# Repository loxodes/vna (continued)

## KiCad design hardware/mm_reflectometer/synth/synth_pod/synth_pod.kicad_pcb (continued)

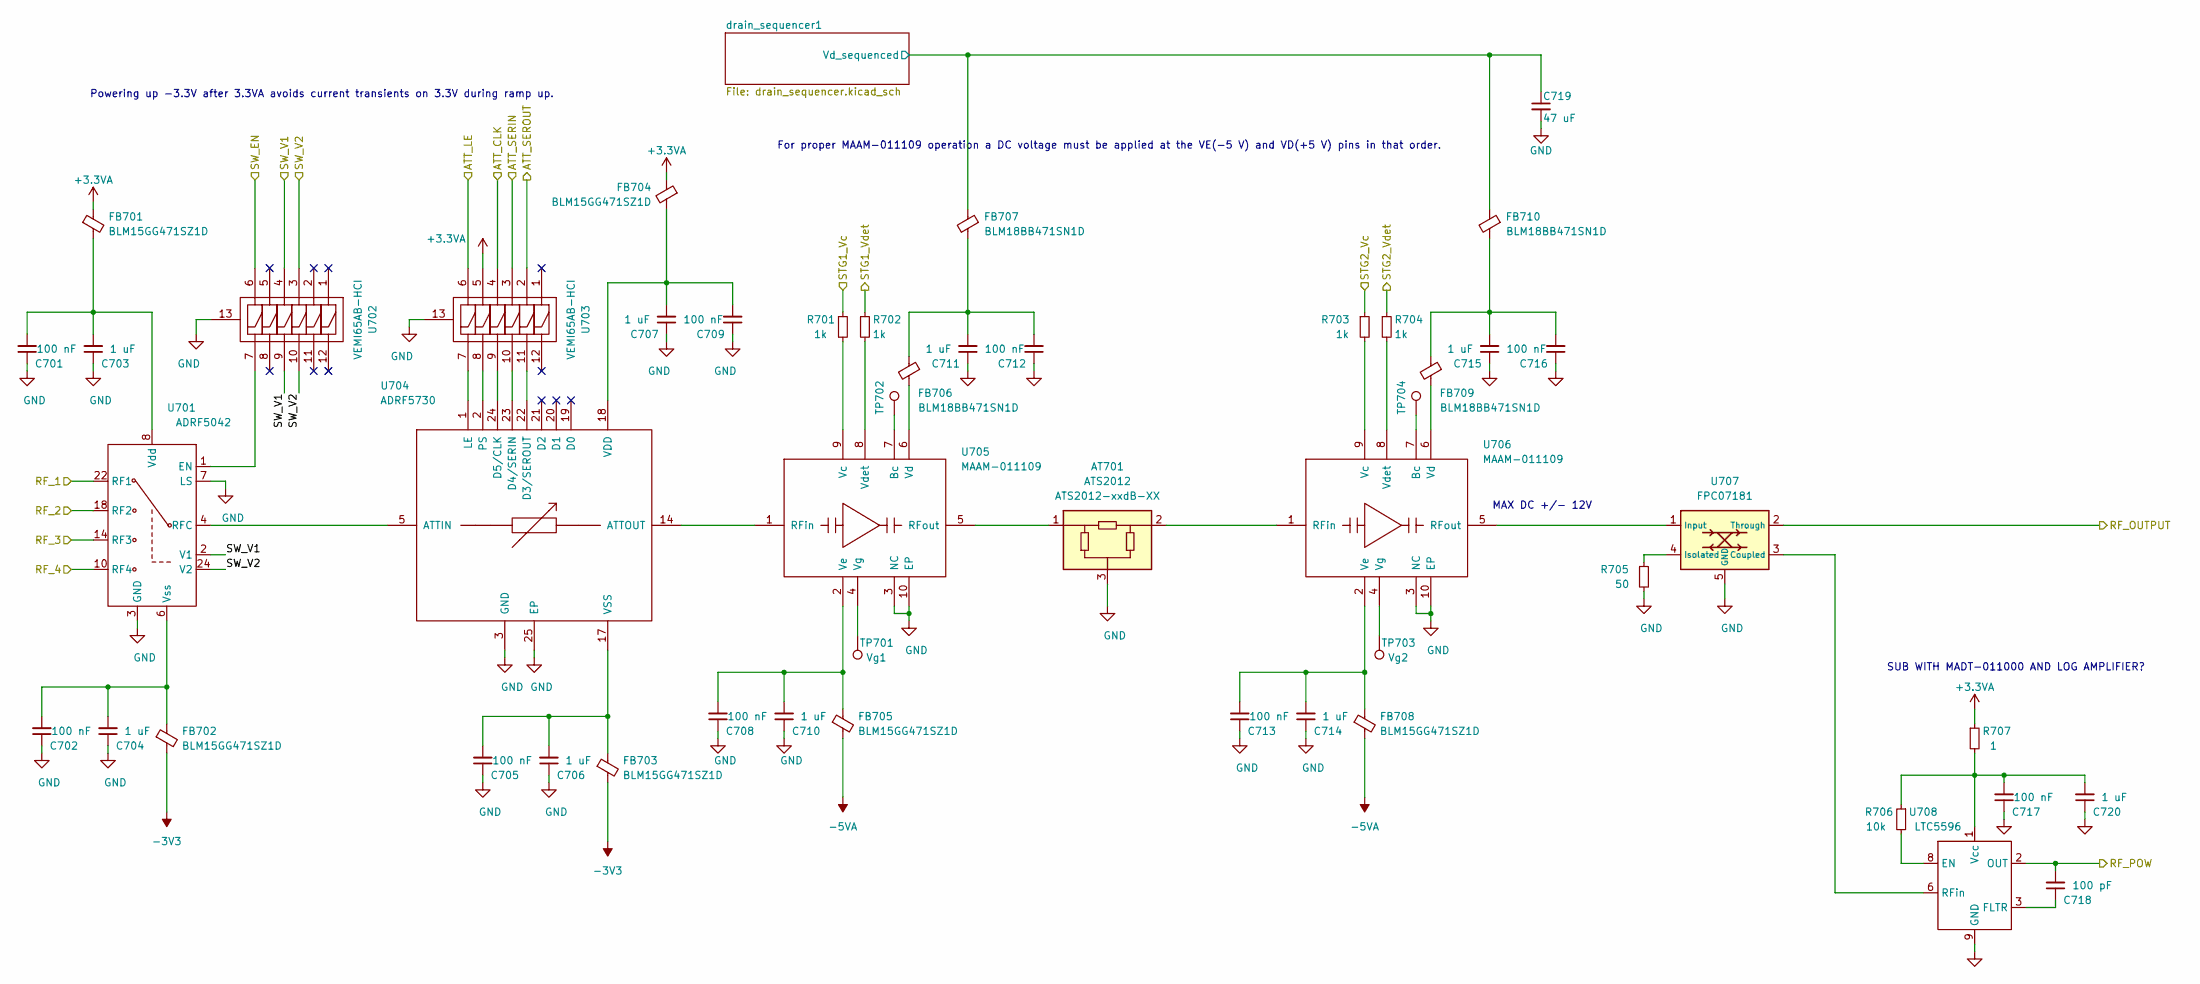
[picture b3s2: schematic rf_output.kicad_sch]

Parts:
AT701: ATS2012; mpn ATS2012-xxdB-XX
C701, C702, C705, C708, C709, C712, C713, C716, C717: 100 nF; C_0402_1005Metric
C703, C704, C706, C707, C710, C711, C714, C715, C720: 1 uF; C_0402_1005Metric
C718: 100 pF; C_0402_1005Metric
C719: 47 uF; CP_EIA-3528-15_AVX-H
FB701, FB702, FB703, FB704, FB705, FB708: BLM15GG471SZ1D; L_0402_1005Metric
FB706, FB707, FB709, FB710: BLM18BB471SN1D; L_0603_1608Metric
R701, R702, R703, R704: 1k; R_0402_1005Metric
R705: 50; R_0402_1005Metric
R706: 10k; R_0402_1005Metric
R707: 1; R_0402_1005Metric
TP701: Vg1; TestPoint_Pad_D1.5mm
TP702: Bc1; TestPoint_Pad_D1.5mm
TP703: Vg2; TestPoint_Pad_D1.5mm
TP704: Bc2; TestPoint_Pad_D1.5mm
U701: ADRF5042; LGA-24-1EP_3x3mm_P0.4mm_EP1.5x1.5mm_ADI_CC_24_12; mpn ADRF5042BCCZN; digikey# 505-ADRF5042BCCZN-ND
U702, U703: VEMI65AB-HCI; LLP2513-13L
U704: ADRF5730; LGA-24_EP_4x4_Pitch0.5mm; mpn ADRF5730BCCZN; digikey# ADRF5730BCCZN-ND
U705, U706: MAAM-011109; MACOM_LGA9; mpn MAAM-011109-TR1000; digikey# 1465-1284-1-ND
U707: FPC07181; mpn FPC07181; digikey# 1761-1032-ND
U708: LTC5596; DFN-8-1EP_2x2mm_P0.5mm_EP0.25x1.6mm

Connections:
+3.3VA: FB701.1, FB704.1, R707.1, U703.5; also elsewhere on the board
-3V3: FB702.2, FB703.2; also elsewhere on the board
-5VA: FB705.2, FB708.2; also elsewhere on the board
/ATT_CLK: U703.4; also elsewhere on the board
/ATT_LE: U703.6; also elsewhere on the board
/ATT_SERIN: U703.3; also elsewhere on the board
/ATT_SEROUT: U703.2; also elsewhere on the board
/OUT_SW_EN: U702.6; also elsewhere on the board
/OUT_SW_V1: U701.2 (V1), U702.4, U702.9; also elsewhere on the board
/OUT_SW_V2: U701.24 (V2), U702.3, U702.10; also elsewhere on the board
/RF_POW: C718.2, U708.2 (OUT); also elsewhere on the board
/STG1_Vc: R701.1; also elsewhere on the board
/STG1_Vdet: R702.1; also elsewhere on the board
/STG2_Vc: R703.1; also elsewhere on the board
/STG2_Vdet: R704.1; also elsewhere on the board
/bypass/BYPASS_OUT: U701.22 (RF1); also elsewhere on the board
/fundamental_a/FUND_A_OUT: U701.18 (RF2); also elsewhere on the board
/fundamental_b/FUND_B_OUT: U701.14 (RF3); also elsewhere on the board
/highband/HIGHBAND_OUT: U701.10 (RF4); also elsewhere on the board
/panel/RF_OUTPUT: U707.2 (Through); also elsewhere on the board
/rf_output/drain_sequencer1/Vd_sequenced: C719.1, FB707.1, FB710.1; also elsewhere on the board
GND: AT701.3, C701.1, C702.1, C703.1, C704.1, C705.1, C706.1, C707.1, C708.1, C709.1, C710.1, C711.1, C712.1, C713.1, C714.1, C715.1, C716.1, C717.1, C719.2, C720.1, R705.2, U701.3 (GND), U701.5 (GND), U701.7 (LS), U701.9 (GND), U701.11 (GND), U701.12 (GND), U701.13 (GND), U701.15 (GND), U701.16 (GND), U701.17 (GND), U701.19 (GND), U701.20 (GND), U701.21 (GND), U701.23 (GND), U701.25 (GND), U702.13, U703.13, U704.3 (GND), U704.4 (GND), U704.6 (GND), U704.7 (GND), U704.8 (GND), U704.9 (GND), U704.10 (GND), U704.11 (GND), U704.12 (GND), U704.13 (GND), U704.15 (GND), U704.16 (GND), U704.25 (EP), U705.3 (NC), U705.10 (EP), U706.3 (NC), U706.10 (EP), U707.5 (GND), U708.4 (GND), U708.5 (GND), U708.7 (GND), U708.9 (GND); also elsewhere on the board
unnamed: AT701.1, U705.5 (RFout)
unnamed: AT701.2, U706.1 (RFin)
unnamed: C701.2, C703.2, FB701.2, U701.8 (Vdd)
unnamed: C702.2, C704.2, FB702.1, U701.6 (Vss)
unnamed: C705.2, C706.2, FB703.1, U704.17 (VSS)
unnamed: C707.2, C709.2, FB704.2, U704.18 (VDD)
unnamed: C708.2, C710.2, FB705.1, U705.2 (Ve)
unnamed: C711.2, C712.2, FB706.1, FB707.2
unnamed: C713.2, C714.2, FB708.1, U706.2 (Ve)
unnamed: C715.2, C716.2, FB709.1, FB710.2
unnamed: C717.2, C720.2, R706.1, R707.2, U708.1 (Vcc)
unnamed: C718.1, U708.3 (FLTR)
unnamed: FB706.2, U705.6 (Vd)
unnamed: FB709.2, U706.6 (Vd)
unnamed: R701.2, U705.9 (Vc)
unnamed: R702.2, U705.8 (Vdet)
unnamed: R703.2, U706.9 (Vc)
unnamed: R704.2, U706.8 (Vdet)
unnamed: R705.1, U707.4 (Isolated)
unnamed: R706.2, U708.8 (EN)
unnamed: TP701.1, U705.4 (Vg)
unnamed: TP702.1, U705.7 (Bc)
unnamed: TP703.1, U706.4 (Vg)
unnamed: TP704.1, U706.7 (Bc)
unnamed: U701.1 (EN), U702.7
unnamed: U701.4 (RFC), U704.5 (ATTIN)
unnamed: U703.7, U704.1 (LE)
unnamed: U703.8, U704.2 (PS)
unnamed: U703.9, U704.24 (D5/CLK)
unnamed: U703.10, U704.23 (D4/SERIN)
unnamed: U703.11, U704.22 (D3/SEROUT)
unnamed: U704.14 (ATTOUT), U705.1 (RFin)
unnamed: U706.5 (RFout), U707.1 (Input)
unnamed: U707.3 (Coupled), U708.6 (RFin)

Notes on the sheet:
Powering up -3.3V after 3.3VA avoids current transients on 3.3V during ramp up.
MAX DC +/- 12V
For proper MAAM-011109 operation a DC voltage must be applied at the VE(-5 V) and VD(+5 V) pins in that order.
SUB WITH MADT-011000 AND LOG AMPLIFIER?

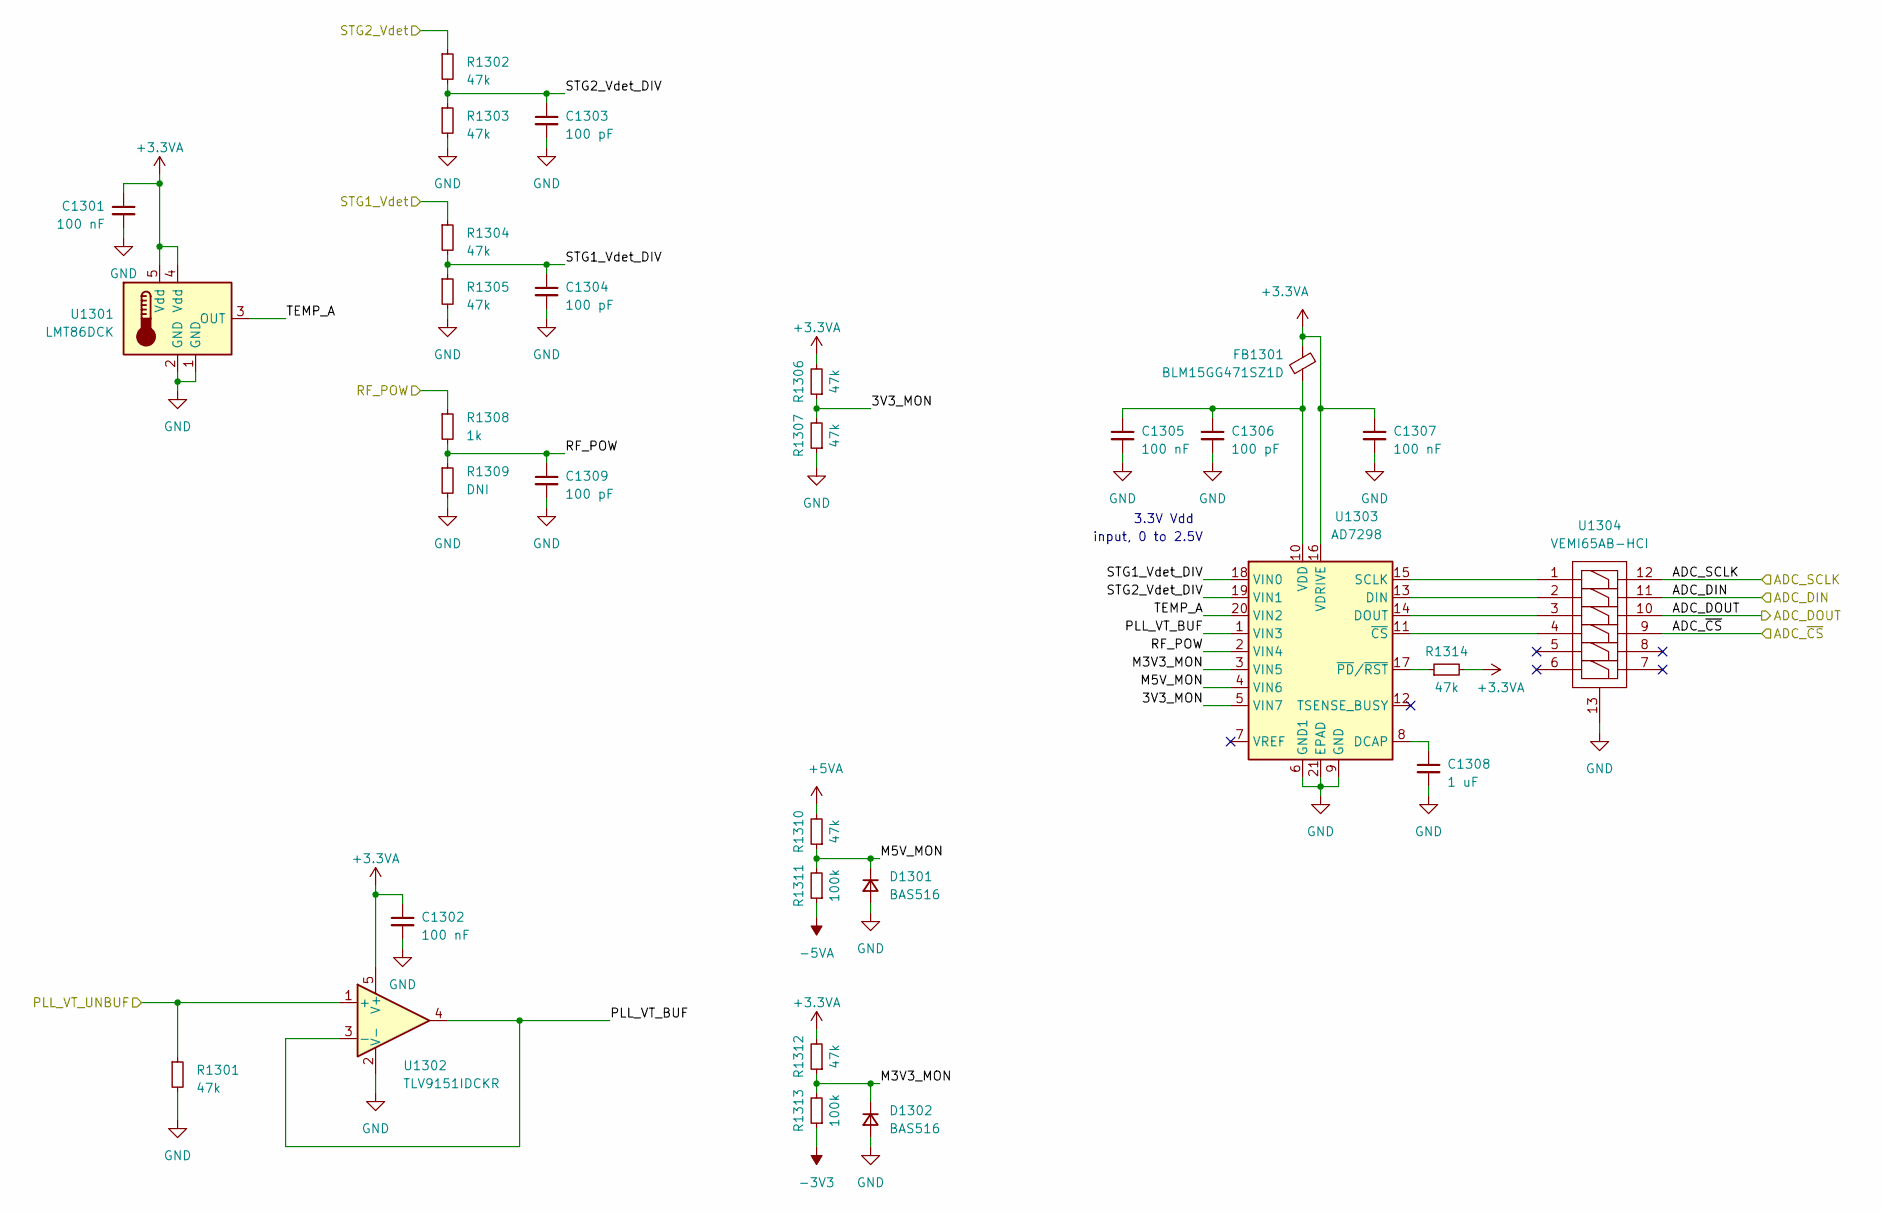
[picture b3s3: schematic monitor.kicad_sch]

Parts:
C1301, C1302, C1305, C1307: 100 nF; C_0402_1005Metric
C1303, C1304, C1306, C1309: 100 pF; C_0402_1005Metric
C1308: 1 uF; C_0402_1005Metric
D1301, D1302: BAS516; D_SOD-523
FB1301: BLM15GG471SZ1D; L_0402_1005Metric
R1301, R1302, R1303, R1304, R1305, R1306, R1307, R1310, R1312, R1314: 47k; R_0402_1005Metric
R1308: 1k; R_0402_1005Metric
R1309: DNI; R_0402_1005Metric
R1311, R1313: 100k; R_0402_1005Metric
U1301: LMT86DCK; SOT-353_SC-70-5
U1302: TLV9151IDCKR; SOT-353_SC-70-5
U1303: AD7298; LFCSP-20-1EP_4x4mm_P0.5mm_EP2.6x2.6mm_ThermalVias
U1304: VEMI65AB-HCI; LLP2513-13L

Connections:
+3.3VA: C1301.1, C1302.1, C1307.1, FB1301.1, R1306.2, R1312.2, R1314.2, U1301.4 (Vdd), U1301.5 (Vdd), U1302.5 (V+), U1303.16 (VDRIVE); also elsewhere on the board
+5VA: R1310.2; also elsewhere on the board
-3V3: R1313.1; also elsewhere on the board
-5VA: R1311.1; also elsewhere on the board
/PLL_VT_UNBUF: R1301.1, U1302.1 (+); also elsewhere on the board
/RF_POW: C1309.1, R1308.1, R1308.2, R1309.1, U1303.2 (VIN4); also elsewhere on the board
/STG1_Vdet: R1304.1; also elsewhere on the board
/STG2_Vdet: R1302.1; also elsewhere on the board
/TLM_ADC_DIN: U1304.11; also elsewhere on the board
/TLM_ADC_DOUT: U1304.10; also elsewhere on the board
/TLM_ADC_SCLK: U1304.12; also elsewhere on the board
/TLM_ADC_~CS: U1304.9; also elsewhere on the board
/monitor/3V3_MON: R1306.1, R1307.2, U1303.5 (VIN7)
/monitor/M3V3_MON: D1302.1 (K), R1312.1, R1313.2, U1303.3 (VIN5)
/monitor/M5V_MON: D1301.1 (K), R1310.1, R1311.2, U1303.4 (VIN6)
/monitor/PLL_VT_BUF: U1302.3 (-), U1302.4, U1303.1 (VIN3)
/monitor/STG1_Vdet_DIV: C1304.1, R1304.2, R1305.1, U1303.18 (VIN0)
/monitor/STG2_Vdet_DIV: C1303.1, R1302.2, R1303.1, U1303.19 (VIN1)
/monitor/TEMP_A: U1301.3 (OUT), U1303.20 (VIN2)
GND: C1301.2, C1302.2, C1303.2, C1304.2, C1305.2, C1306.2, C1307.2, C1308.2, C1309.2, D1301.2 (A), D1302.2 (A), R1301.2, R1303.2, R1305.2, R1307.1, R1309.2, U1301.1 (GND), U1301.2 (GND), U1302.2 (V-), U1303.6 (GND1), U1303.9 (GND), U1303.21 (EPAD), U1304.13; also elsewhere on the board
unnamed: C1305.1, C1306.1, FB1301.2, U1303.10 (VDD)
unnamed: C1308.1, U1303.8 (DCAP)
unnamed: R1314.1, U1303.17 (~PD/~RST)
unnamed: U1303.11 (~CS), U1304.4
unnamed: U1303.13 (DIN), U1304.2
unnamed: U1303.14 (DOUT), U1304.3
unnamed: U1303.15 (SCLK), U1304.1

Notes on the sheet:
3.3V Vdd
input, 0 to 2.5V

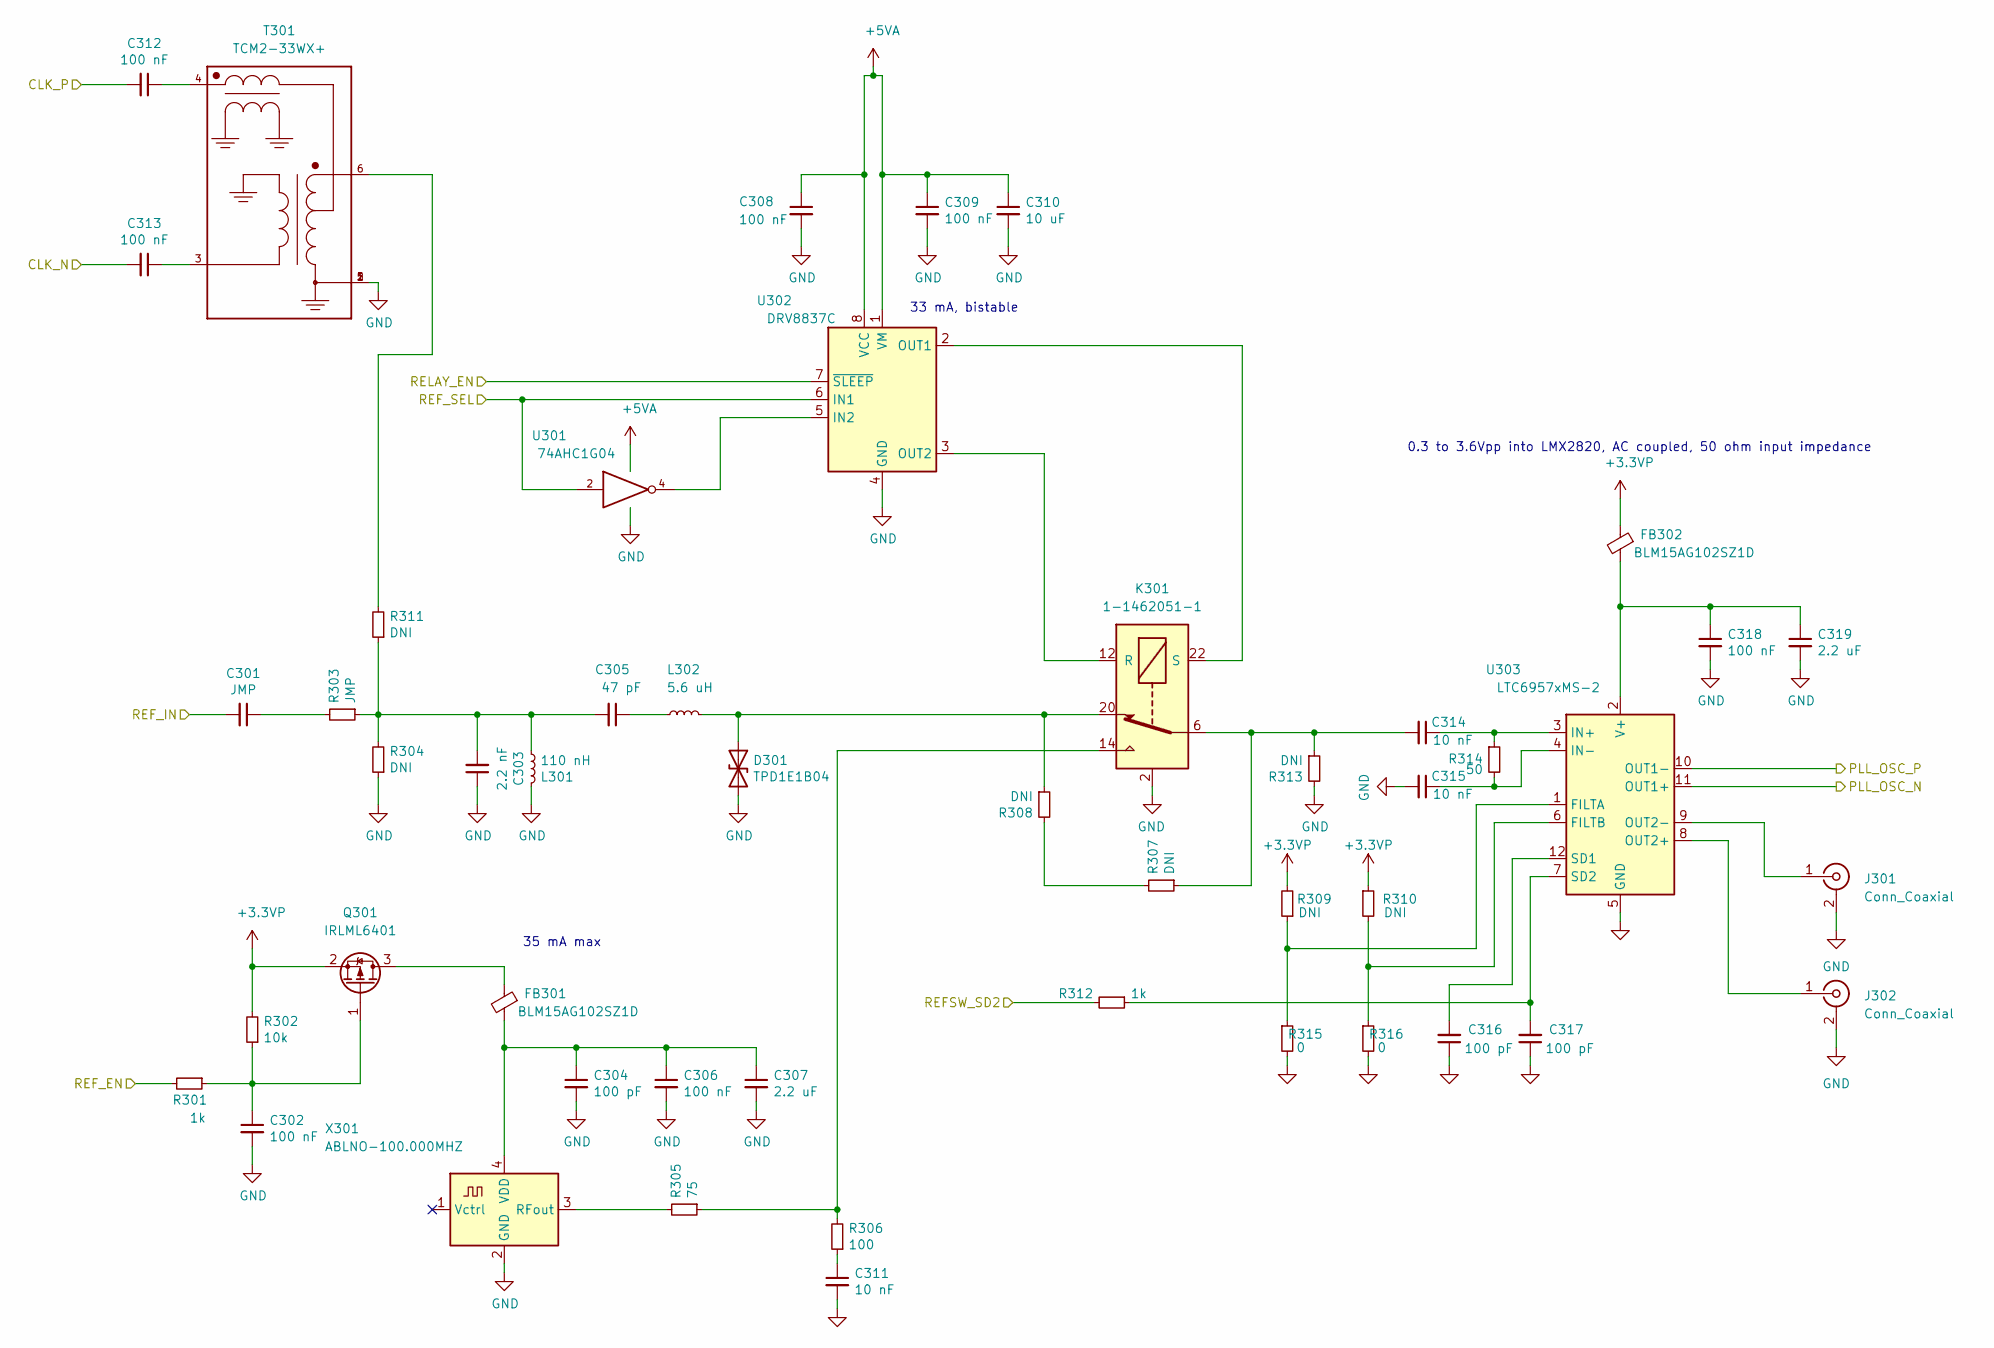
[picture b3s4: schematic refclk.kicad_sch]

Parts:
C301: JMP; C_0402_1005Metric
C302, C306, C308, C309, C312, C313, C318: 100 nF; C_0402_1005Metric
C303: 2.2 nF; C_0402_1005Metric
C304, C316, C317: 100 pF; C_0402_1005Metric
C305: 47 pF; C_0402_1005Metric
C307, C319: 2.2 uF; C_0603_1608Metric
C310: 10 uF; C_0805_2012Metric
C311, C314, C315: 10 nF; C_0402_1005Metric
D301: TPD1E1B04; D_0402_1005Metric
FB301, FB302: BLM15AG102SZ1D; L_0402_1005Metric
J301, J302: Conn_Coaxial; SMA_Amphenol_132134-16_Vertical
K301: 1-1462051-1; Relay_SPDT_AXICOM_HF3Series_50ohms_Pitch1.27mm
L301: 110 nH; L_0603_1608Metric
L302: 5.6 uH; L_0805_2012Metric
Q301: IRLML6401; SOT-23
R301, R312: 1k; R_0402_1005Metric
R302: 10k; R_0402_1005Metric
R303: JMP; R_0402_1005Metric
R304, R307, R308, R309, R310, R311, R313: DNI; R_0402_1005Metric
R305: 75; R_0402_1005Metric
R306: 100; R_0402_1005Metric
R314: 50; R_0402_1005Metric
R315, R316: 0; R_0402_1005Metric
T301: TCM2-33WX+; XFMR_TCM2-33WX+; PARTREV A
U301: 74AHC1G04; SOT-353_SC-70-5
U302: DRV8837C; WSON-8-1EP_2x2mm_P0.5mm_EP0.9x1.6mm
U303: LTC6957xMS-2; MSOP-12_3x4mm_P0.65mm
X301: ABLNO-100.000MHZ; Oscillator_SMD_Abracon_ABLNO

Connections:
+3.3VP: FB302.1, Q301.2 (S), R302.2, R309.2, R310.1; also elsewhere on the board
+5VA: C308.1, C309.1, C310.1, U301.5 (VCC), U302.1 (VM), U302.8 (VCC); also elsewhere on the board
/REFSW_SD2: R312.2; also elsewhere on the board
/REF_EN: R301.2; also elsewhere on the board
/REF_IN: C301.2; also elsewhere on the board
/REF_SEL: U301.2, U302.6 (IN1); also elsewhere on the board
/RELAY_EN: U302.7 (~SLEEP); also elsewhere on the board
/refclk/CLK_N: C313.2
/refclk/CLK_P: C312.2
/refclk/PLL_OSC_N: U303.11 (OUT1+); also elsewhere on the board
/refclk/PLL_OSC_P: U303.10 (OUT1-); also elsewhere on the board
GND: C302.2, C303.1, C304.2, C306.2, C307.2, C308.2, C309.2, C310.2, C311.2, C315.2, C316.1, C317.1, C318.2, C319.2, D301.2 (A2), J301.2 (Ext), J302.2 (Ext), K301.2, K301.5, K301.7, K301.10, K301.13, K301.15, K301.17, K301.19, K301.21, L301.1, R304.1, R313.2, R315.2, R316.2, T301.1, T301.2, T301.5, U301.3 (GND), U302.4 (GND), U302.9 (GND), U303.5 (GND), X301.2 (GND); also elsewhere on the board
unnamed: C301.1, R303.2
unnamed: C302.1, Q301.1 (G), R301.1, R302.1
unnamed: C303.2, C305.2, L301.2, R303.1, R304.2, R311.1
unnamed: C304.1, C306.1, C307.1, FB301.2, X301.4 (VDD)
unnamed: C305.1, L302.2
unnamed: C311.1, R306.1
unnamed: C312.1, T301.4
unnamed: C313.1, T301.3
unnamed: C314.1, R314.1, U303.3 (IN+)
unnamed: C314.2, K301.6, R307.1, R313.1
unnamed: C315.1, R314.2, U303.4 (IN-)
unnamed: C316.2, U303.12 (SD1)
unnamed: C317.2, R312.1, U303.7 (SD2)
unnamed: C318.1, C319.1, FB302.2, U303.2 (V+)
unnamed: D301.1 (A1), K301.20, L302.1, R308.1
unnamed: FB301.1, Q301.3 (D)
unnamed: J301.1 (In), U303.9 (OUT2-)
unnamed: J302.1 (In), U303.8 (OUT2+)
unnamed: K301.1, K301.12 (R), U302.3 (OUT2)
unnamed: K301.11, K301.22 (S), U302.2 (OUT1)
unnamed: K301.14, R305.1, R306.2
unnamed: R305.2, X301.3 (RFout)
unnamed: R307.2, R308.2
unnamed: R309.1, R315.1, U303.1 (FILTA)
unnamed: R310.2, R316.1, U303.6 (FILTB)
unnamed: R311.2, T301.6
unnamed: U301.4, U302.5 (IN2)

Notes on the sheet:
33 mA, bistable
0.3 to 3.6Vpp into LMX2820, AC coupled, 50 ohm input impedance
35 mA max

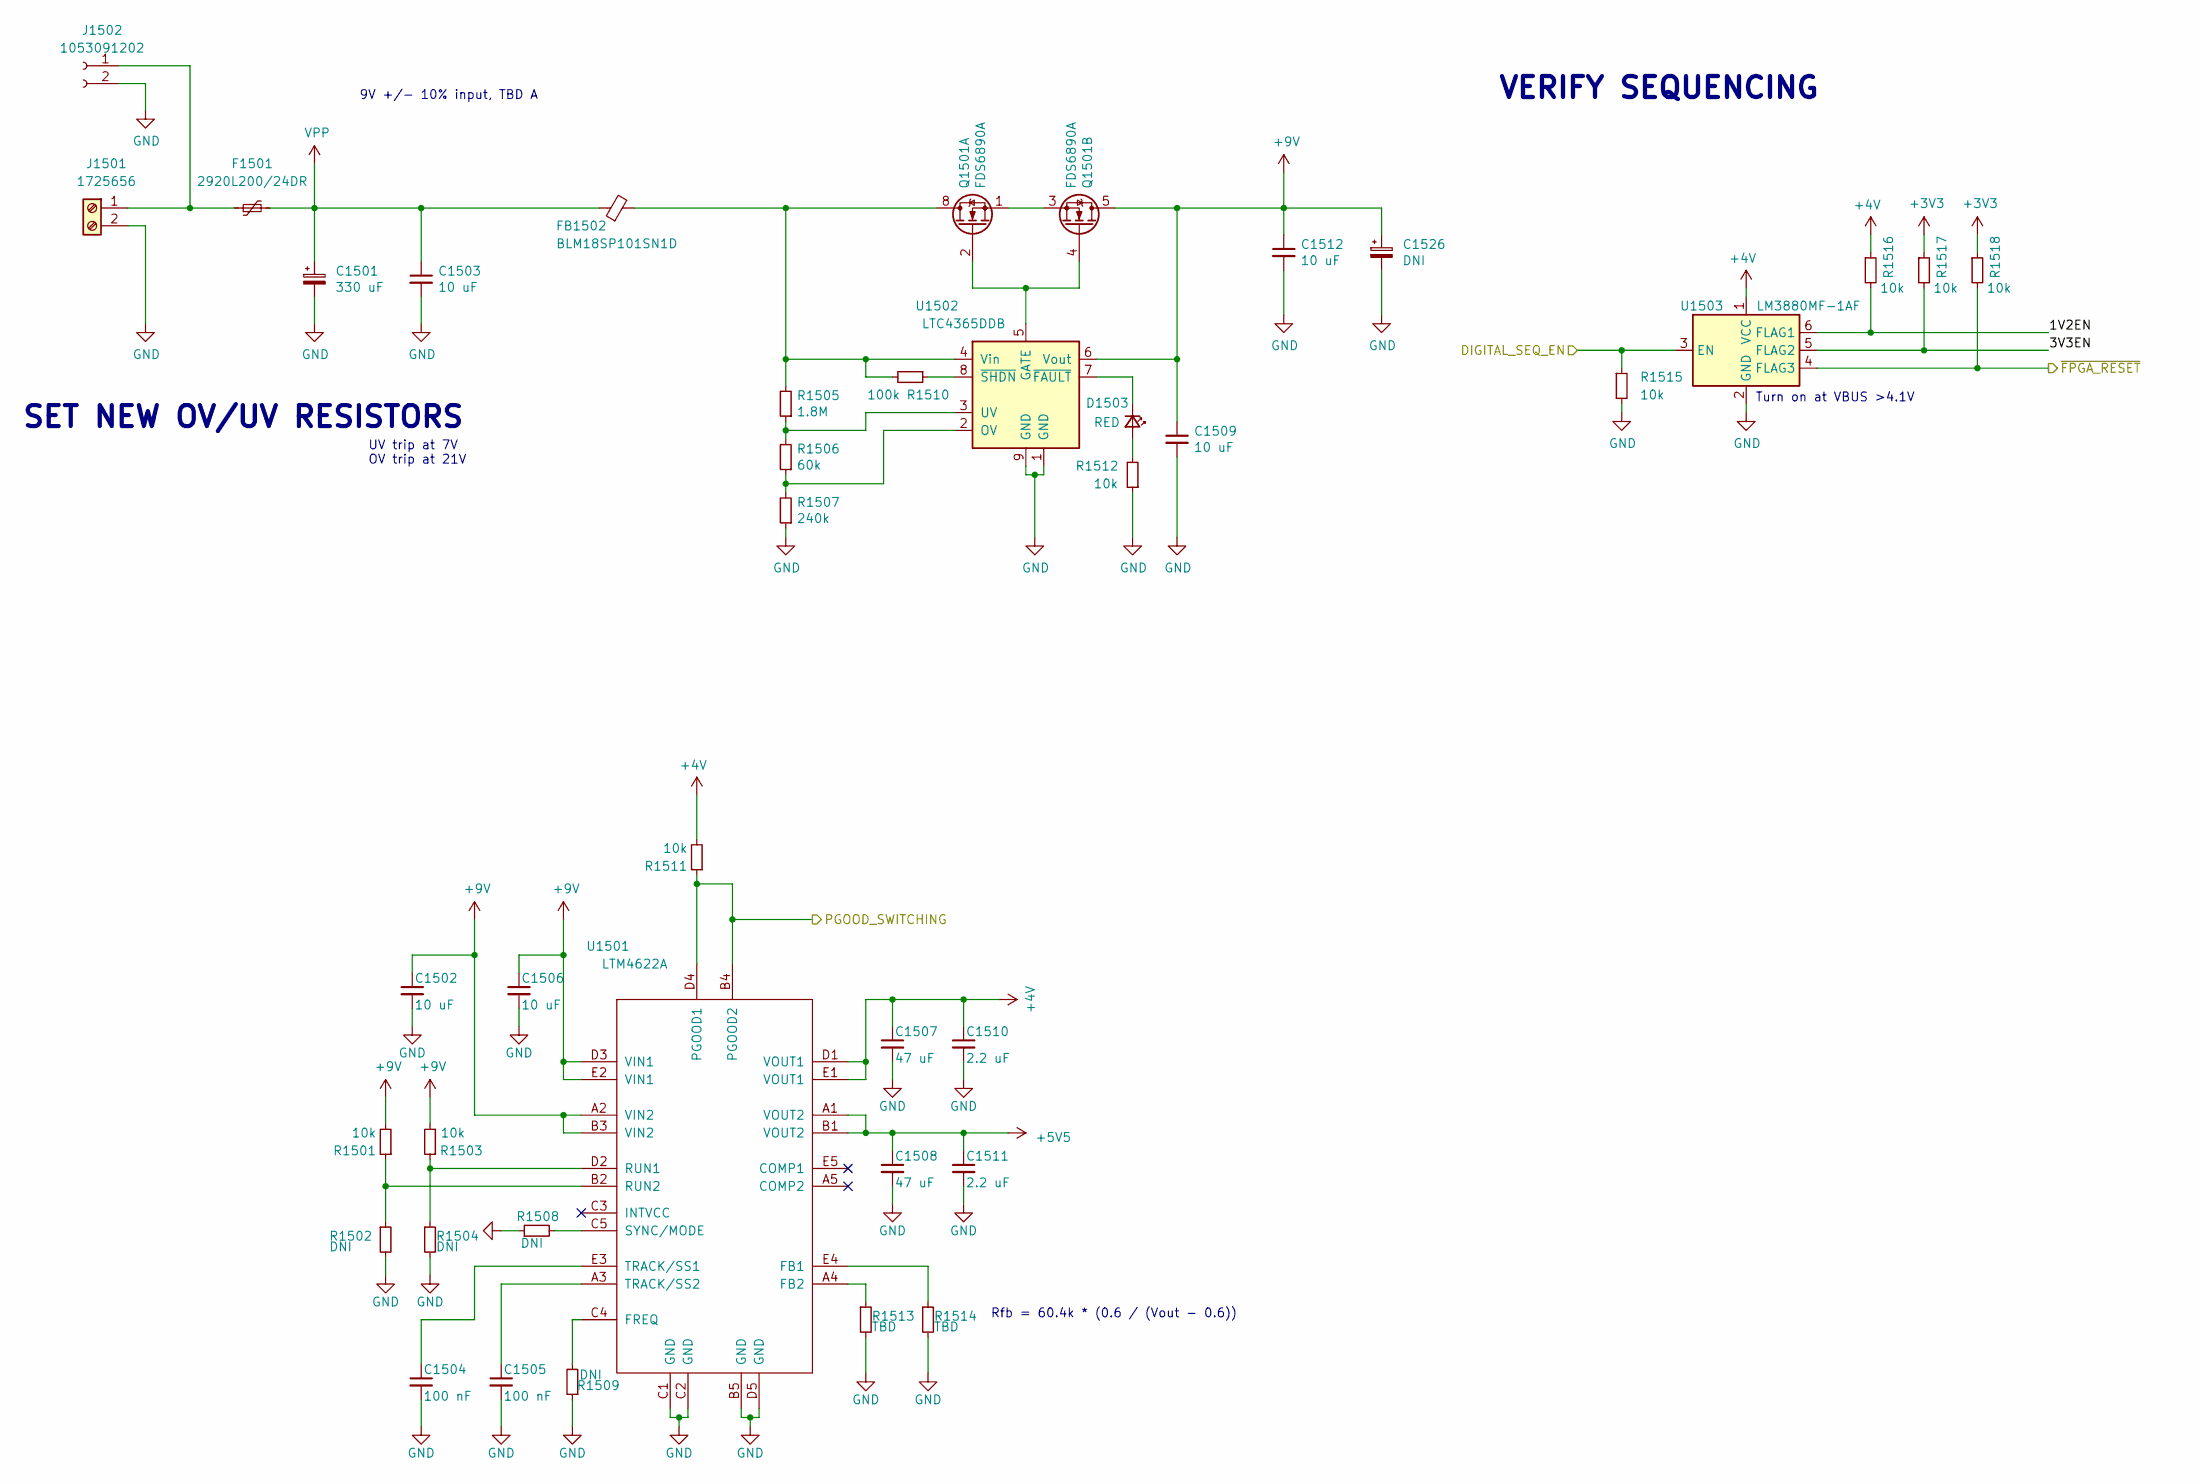
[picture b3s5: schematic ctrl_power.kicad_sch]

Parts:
C1501: 330 uF; CP_Elec_10x12.5
C1502, C1503, C1506, C1509, C1512: 10 uF; C_0805_2012Metric
C1504, C1505: 100 nF; C_0402_1005Metric
C1507, C1508: 47 uF; CP_EIA-3528-15_AVX-H
C1510, C1511: 2.2 uF; C_0603_1608Metric
C1526: DNI; CP_Elec_10x12.5
D1503: RED; LED_0603_1608Metric
F1501: 2920L200/24DR; Fuse_2920_7451Metric
FB1502: BLM18SP101SN1D; L_0603_1608Metric
J1501: 1725656; TerminalBlock_Phoenix_MPT-0,5-2-2.54_1x02_P2.54mm_Horizontal
J1502: 1053091202; Molex_Nano-Fit_105309-xx02_1x02_P2.50mm_Vertical
Q1501: FDS6890A; SOIC-8_3.9x4.9mm_P1.27mm
R1501, R1503, R1511, R1512, R1515, R1516, R1517, R1518: 10k; R_0402_1005Metric
R1502, R1504, R1508, R1509: DNI; R_0402_1005Metric
R1505: 1.8M; R_0402_1005Metric
R1506: 60k; R_0402_1005Metric
R1507: 240k; R_0402_1005Metric
R1510: 100k; R_0402_1005Metric
R1513, R1514: TBD; R_0402_1005Metric
U1501: LTM4622A; BGA-25_5x5_6.35x6.35mm
U1502: LTC4365DDB; DFN-8-1EP_2x3mm_P0.5mm_EP0.61x2.2mm
U1503: LM3880MF-1AF; SOT-23-6; MPN LM3880MFX-1AF/NOPB

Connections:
+4V: C1507.1, C1510.1, R1511.2, R1516.1, U1501.D1 (VOUT1), U1501.E1 (VOUT1), U1503.1 (VCC); also elsewhere on the board
+5V5: C1508.1, C1511.1, U1501.A1 (VOUT2), U1501.B1 (VOUT2); also elsewhere on the board
+9V: C1502.1, C1506.1, C1509.1, C1512.1, C1526.1, Q1501.5 (D2), Q1501.6 (D2), R1501.2, R1503.2, U1501.A2 (VIN2), U1501.B3 (VIN2), U1501.D3 (VIN1), U1501.E2 (VIN1), U1502.6 (Vout)
/ctrl_power/1V2EN: R1516.2, U1503.6 (FLAG1)
/ctrl_power/3V3EN: R1517.2, U1503.5 (FLAG2)
/ctrl_power/PGOOD_SWITCHING: R1511.1, U1501.B4 (PGOOD2), U1501.D4 (PGOOD1); also elsewhere on the board
/ctrl_power/~FPGA_RESET: R1518.2, U1503.4 (FLAG3); also elsewhere on the board
/rf_power/15V_BIAS_EN: R1515.1, U1503.3 (EN); also elsewhere on the board
GND: C1501.2, C1502.2, C1503.2, C1504.2, C1505.2, C1506.2, C1507.2, C1508.2, C1509.2, C1510.2, C1511.2, C1512.2, C1526.2, J1501.2, J1502.2, R1502.2, R1504.2, R1507.1, R1508.1, R1509.1, R1512.1, R1513.2, R1514.2, R1515.2, U1501.B5 (GND), U1501.C1 (GND), U1501.C2 (GND), U1501.D5 (GND), U1502.1 (GND), U1502.9 (GND), U1503.2 (GND); also elsewhere on the board
unnamed: C1504.1, U1501.E3 (TRACK/SS1)
unnamed: C1505.1, U1501.A3 (TRACK/SS2)
unnamed: D1503.1 (K), U1502.7 (~FAULT)
unnamed: D1503.2 (A), R1512.2
unnamed: F1501.1, J1501.1, J1502.1
unnamed: Q1501.1 (S1), Q1501.3 (S2)
unnamed: Q1501.2 (G1), Q1501.4 (G2), U1502.5 (GATE)
unnamed: FB1502.2, Q1501.7 (D1), Q1501.8 (D1), R1505.2, R1510.2, U1502.4 (Vin)
unnamed: R1501.1, R1502.1, U1501.B2 (RUN2)
unnamed: R1503.1, R1504.1, U1501.D2 (RUN1)
unnamed: R1505.1, R1506.2, U1502.3 (UV)
unnamed: R1506.1, R1507.2, U1502.2 (OV)
unnamed: R1508.2, U1501.C5 (SYNC/MODE)
unnamed: R1509.2, U1501.C4 (FREQ)
unnamed: R1510.1, U1502.8 (~SHDN)
unnamed: R1513.1, U1501.A4 (FB2)
unnamed: R1514.1, U1501.E4 (FB1)
VPP: C1501.1, C1503.1, F1501.2, FB1502.1

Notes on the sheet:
UV trip at 7V OV trip at 21V
SET NEW OV/UV RESISTORS
Turn on at VBUS >4.1V
9V +/- 10% input, TBD A
VERIFY SEQUENCING
Rfb = 60.4k * (0.6 / (Vout - 0.6))

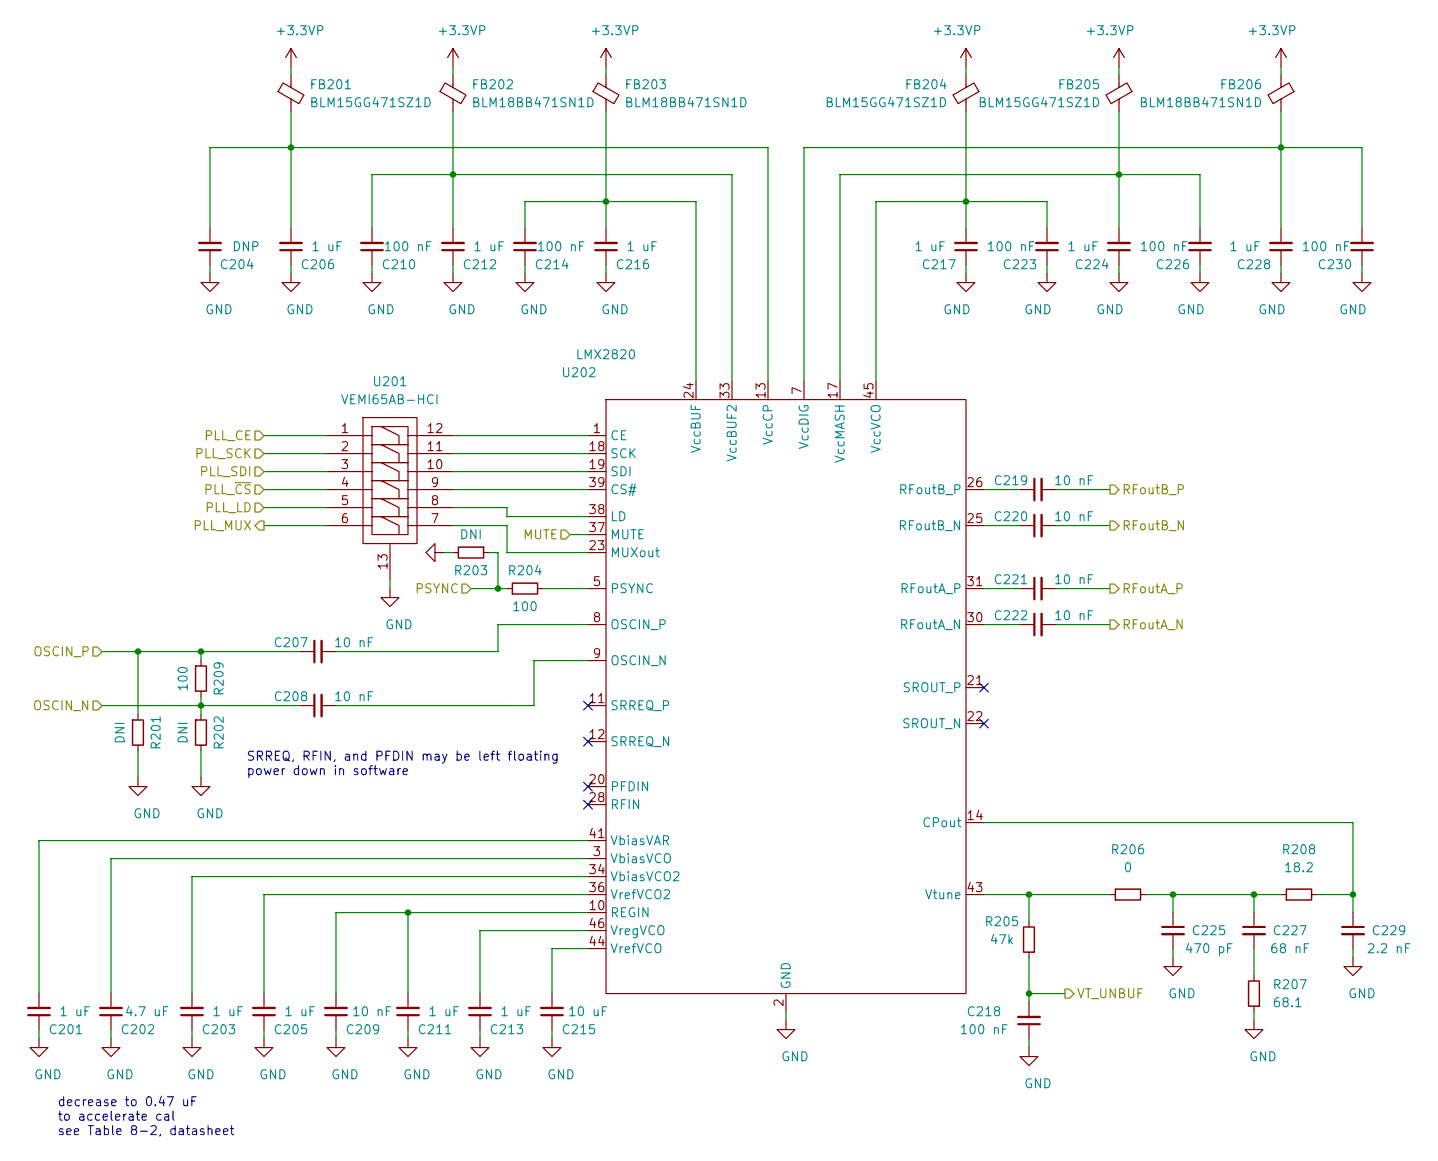
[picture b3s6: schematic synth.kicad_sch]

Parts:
C201, C203, C205, C206, C211, C212, C213, C216, C217, C224, C228: 1 uF; C_0402_1005Metric
C202: 4.7 uF; C_0603_1608Metric
C204: DNP; C_0402_1005Metric
C207, C208, C209, C219, C220, C221, C222: 10 nF; C_0402_1005Metric
C210, C214, C223, C226, C230: 100 nF; C_0402_1005Metric
C215: 10 uF; C_0603_1608Metric
C218: 100 nF; C_0603_1608Metric
C225: 470 pF; C_0603_1608Metric
C227: 68 nF; C_1206_3216Metric
C229: 2.2 nF; C_0603_1608Metric
FB201, FB204, FB205: BLM15GG471SZ1D; L_0402_1005Metric
FB202, FB203, FB206: BLM18BB471SN1D; L_0603_1608Metric
R201, R202, R203: DNI; R_0402_1005Metric
R204, R209: 100; R_0402_1005Metric
R205: 47k; R_0603_1608Metric
R206: 0; R_0603_1608Metric
R207: 68.1; R_0603_1608Metric
R208: 18.2; R_0603_1608Metric
U201: VEMI65AB-HCI; LLP2513-13L
U202: LMX2820; Texas_S-PVQFN-N48_EP5.15x5.15mm

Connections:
+3.3VP: FB201.1, FB202.1, FB203.1, FB204.1, FB205.1, FB206.1; also elsewhere on the board
/PLL_CE: U201.1; also elsewhere on the board
/PLL_LD: U201.5; also elsewhere on the board
/PLL_MUTE: U202.37 (MUTE); also elsewhere on the board
/PLL_MUX: U201.6; also elsewhere on the board
/PLL_SCK: U201.2; also elsewhere on the board
/PLL_SDI: U201.3; also elsewhere on the board
/PLL_SYNC: R203.1, R204.1; also elsewhere on the board
/PLL_VT_UNBUF: C218.2, R205.1; also elsewhere on the board
/PLL_~CS: U201.4; also elsewhere on the board
/bypass/BYPASS_IN: C221.2; also elsewhere on the board
/fundamental_a/FUND_A_IN: C222.2; also elsewhere on the board
/fundamental_b/FUND_B_IN: C219.2; also elsewhere on the board
/highband/HIGHBAND_IN: C220.2; also elsewhere on the board
/refclk/PLL_OSC_N: C208.1, R202.1, R209.2; also elsewhere on the board
/refclk/PLL_OSC_P: C207.1, R201.1, R209.1; also elsewhere on the board
GND: C201.1, C202.1, C203.1, C204.1, C205.1, C206.1, C209.1, C210.1, C211.1, C212.1, C213.1, C214.1, C215.1, C216.1, C217.1, C218.1, C223.1, C224.1, C225.2, C226.1, C228.1, C229.2, C230.1, R201.2, R202.2, R203.2, R207.1, U201.13, U202.2 (GND), U202.4 (GND), U202.6 (GND), U202.15 (GND), U202.16 (GND), U202.27 (GND), U202.29 (GND), U202.32 (GND), U202.35 (NC), U202.40 (GND), U202.42 (GND), U202.47 (GND), U202.48 (GND), U202.49 (GND); also elsewhere on the board
unnamed: C201.2, U202.41 (VbiasVAR)
unnamed: C202.2, U202.3 (VbiasVCO)
unnamed: C203.2, U202.34 (VbiasVCO2)
unnamed: C204.2, C206.2, FB201.2, U202.13 (VccCP)
unnamed: C205.2, U202.36 (VrefVCO2)
unnamed: C207.2, U202.8 (OSCIN_P)
unnamed: C208.2, U202.9 (OSCIN_N)
unnamed: C209.2, C211.2, U202.10 (REGIN)
unnamed: C210.2, C212.2, FB202.2, U202.33 (VccBUF2)
unnamed: C213.2, U202.46 (VregVCO)
unnamed: C214.2, C216.2, FB203.2, U202.24 (VccBUF)
unnamed: C215.2, U202.44 (VrefVCO)
unnamed: C217.2, C223.2, FB204.2, U202.45 (VccVCO)
unnamed: C219.1, U202.26 (RFoutB_P)
unnamed: C220.1, U202.25 (RFoutB_N)
unnamed: C221.1, U202.31 (RFoutA_P)
unnamed: C222.1, U202.30 (RFoutA_N)
unnamed: C224.2, C226.2, FB205.2, U202.17 (VccMASH)
unnamed: C225.1, C227.1, R206.2, R208.1
unnamed: C227.2, R207.2
unnamed: C228.2, C230.2, FB206.2, U202.7 (VccDIG)
unnamed: C229.1, R208.2, U202.14 (CPout)
unnamed: R204.2, U202.5 (PSYNC)
unnamed: R205.2, R206.1, U202.43 (Vtune)
unnamed: U201.7, U202.23 (MUXout)
unnamed: U201.8, U202.38 (LD)
unnamed: U201.9, U202.39 (CS#)
unnamed: U201.10, U202.19 (SDI)
unnamed: U201.11, U202.18 (SCK)
unnamed: U201.12, U202.1 (CE)

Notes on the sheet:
SRREQ, RFIN, and PFDIN may be left floating power down in software
decrease to 0.47 uF to accelerate cal see Table 8-2, datasheet
